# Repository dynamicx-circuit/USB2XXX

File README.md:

# USB2XXX
使用SL2.1S的一拖四USB方案，包含两个can接口，一个串口和一个DBUS接口

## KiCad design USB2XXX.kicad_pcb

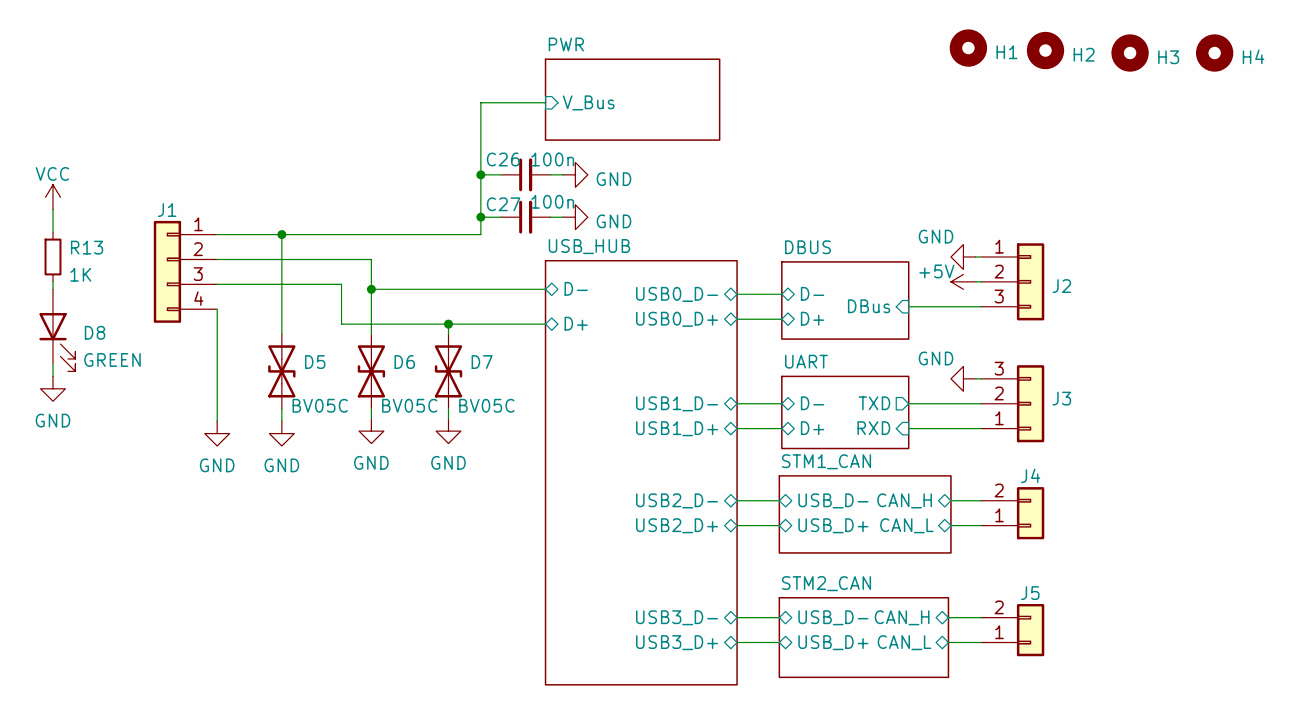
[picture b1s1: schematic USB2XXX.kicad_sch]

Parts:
C26, C27: 100n; C_0603_1608Metric
D5, D6, D7: BV05C; D_SOD-323
D8: GREEN; LED_0603_1608Metric
H1, H2, H3, H4: MountingHole; MountingHole_2.7mm_M2.5
J1: Conn_01x04; Molex_CLIK-Mate_502386-0470_1x04-1MP_P1.25mm_Horizontal
J2, J3: Conn_01x03; JST_GH_SM03B-GHS-TB_1x03-1MP_P1.25mm_Horizontal
J4, J5: Conn_01x02; JST_GH_SM02B-GHS-TB_1x02-1MP_P1.25mm_Horizontal
R13: 1K; R_0603_1608Metric

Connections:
+5V: C26.1, C27.1, D5.2 (A2), J1.1, J2.2; also elsewhere on the board
/DBUS/DBus: J2.3; also elsewhere on the board
/STM1_CAN/CAN_H: J4.2; also elsewhere on the board
/STM1_CAN/CAN_L: J4.1; also elsewhere on the board
/STM2_CAN/CAN_H: J5.2; also elsewhere on the board
/STM2_CAN/CAN_L: J5.1; also elsewhere on the board
/UART/RXD: J3.1; also elsewhere on the board
/UART/TXD: J3.2; also elsewhere on the board
/USB_HUB/D-: D6.2 (A2), J1.2; also elsewhere on the board
GND: C26.2, C27.2, D5.1 (A1), D6.1 (A1), D7.1 (A1), D8.1 (K), J1.4, J2.1, J3.3; also elsewhere on the board
unnamed: D8.2 (A), R13.2

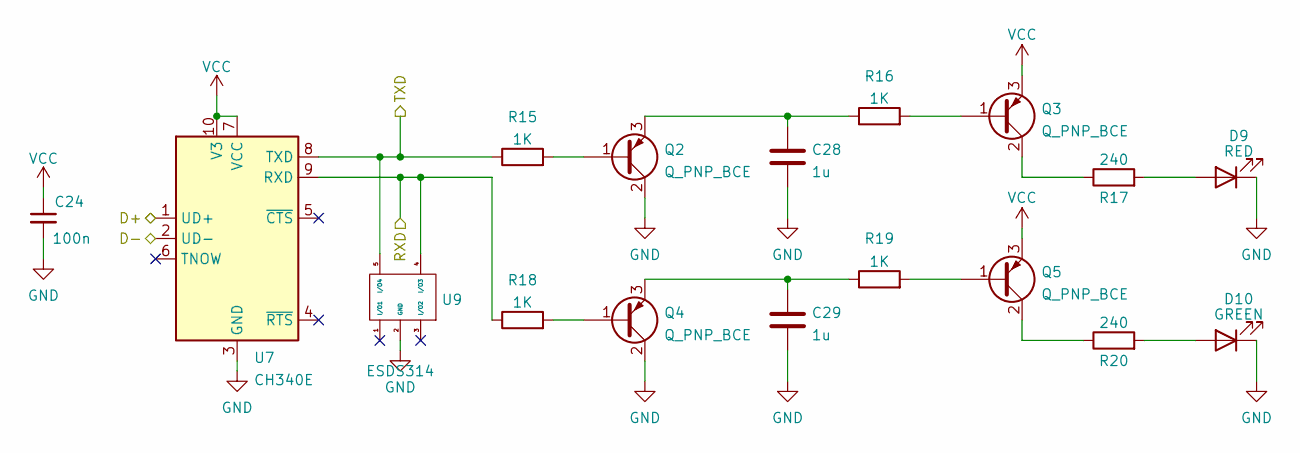
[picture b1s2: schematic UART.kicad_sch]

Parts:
C24: 100n; C_0603_1608Metric
C28, C29: 1u; C_0603_1608Metric
D9: RED; LED_0603_1608Metric
D10: GREEN; LED_0603_1608Metric
Q2, Q3, Q4, Q5: Q_PNP_BCE; SOT-23
R15, R16, R18, R19: 1K; R_0603_1608Metric
R17, R20: 240; R_0603_1608Metric
U7: CH340E; MSOP-10_3x3mm_P0.5mm
U9: ESDS314; SOT-23-5

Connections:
/UART/D+: U7.1 (UD+); also elsewhere on the board
/UART/D-: U7.2 (UD-); also elsewhere on the board
/UART/RXD: R18.1, U7.9 (RXD), U9.4 (I/O3); also elsewhere on the board
/UART/TXD: R15.1, U7.8 (TXD), U9.5 (I/O4); also elsewhere on the board
GND: C24.2, C28.2, C29.2, D9.1 (K), D10.1 (K), Q2.2 (C), Q4.2 (C), U7.3 (GND), U9.2 (GND); also elsewhere on the board
unnamed: D9.2 (A), R17.2
unnamed: D10.2 (A), R20.2
unnamed: Q2.1 (B), R15.2
unnamed: C28.1, Q2.3 (E), R16.1
unnamed: Q3.1 (B), R16.2
unnamed: Q3.2 (C), R17.1
unnamed: Q4.1 (B), R18.2
unnamed: C29.1, Q4.3 (E), R19.1
unnamed: Q5.1 (B), R19.2
unnamed: Q5.2 (C), R20.1

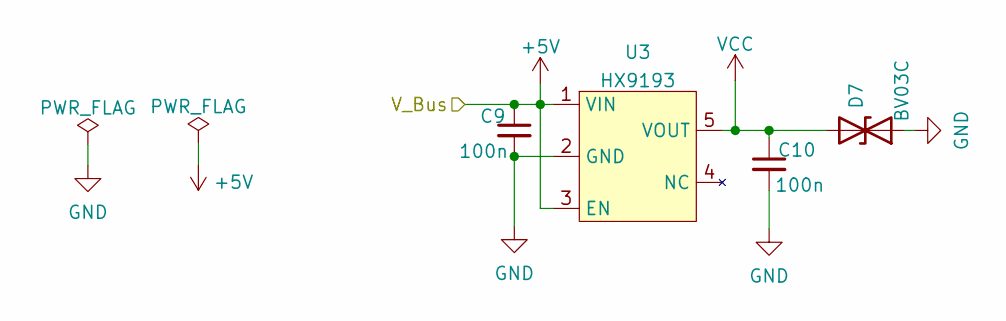
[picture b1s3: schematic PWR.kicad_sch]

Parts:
C9, C10: 100n; C_0603_1608Metric
D7: BV03C; D_SOD-323
U3: HX9193; SOT-23-5_HandSoldering

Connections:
+5V: C9.1, U3.1 (VIN), U3.3 (EN); also elsewhere on the board
GND: C9.2, C10.2, D7.1 (A1), U3.2 (GND); also elsewhere on the board

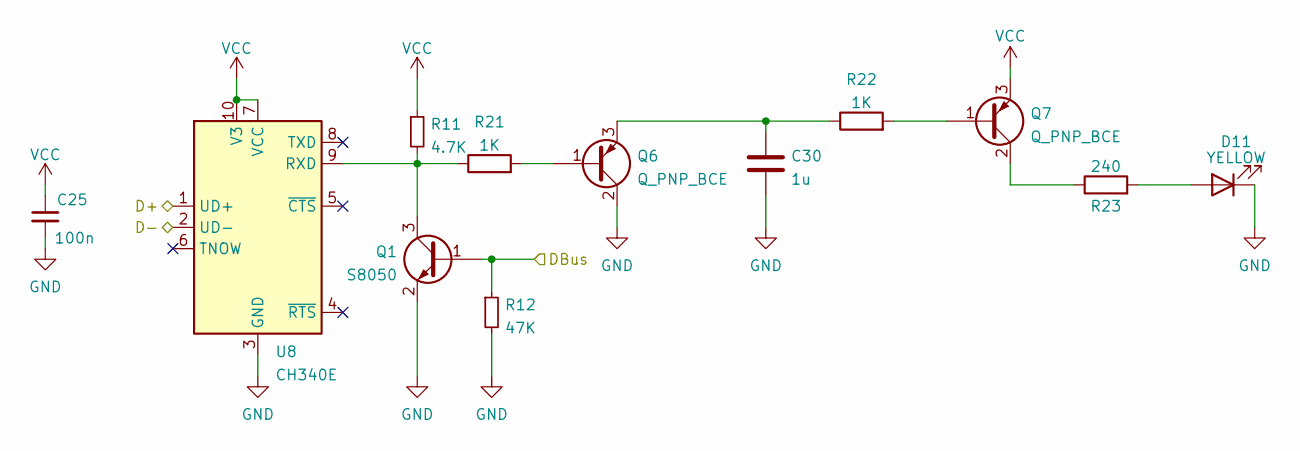
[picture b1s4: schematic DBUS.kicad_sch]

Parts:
C25: 100n; C_0603_1608Metric
C30: 1u; C_0603_1608Metric
D11: YELLOW; LED_0603_1608Metric
Q1: S8050; SOT-23
Q6, Q7: Q_PNP_BCE; SOT-23
R11: 4.7K; R_0603_1608Metric
R12: 47K; R_0603_1608Metric
R21, R22: 1K; R_0603_1608Metric
R23: 240; R_0603_1608Metric
U8: CH340E; MSOP-10_3x3mm_P0.5mm

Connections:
/DBUS/D+: U8.1 (UD+); also elsewhere on the board
/DBUS/D-: U8.2 (UD-); also elsewhere on the board
/DBUS/DBus: Q1.1 (B), R12.1; also elsewhere on the board
GND: C25.2, C30.2, D11.1 (K), Q1.2 (E), Q6.2 (C), R12.2, U8.3 (GND); also elsewhere on the board
unnamed: D11.2 (A), R23.2
unnamed: Q1.3 (C), R11.2, R21.1, U8.9 (RXD)
unnamed: Q6.1 (B), R21.2
unnamed: C30.1, Q6.3 (E), R22.1
unnamed: Q7.1 (B), R22.2
unnamed: Q7.2 (C), R23.1

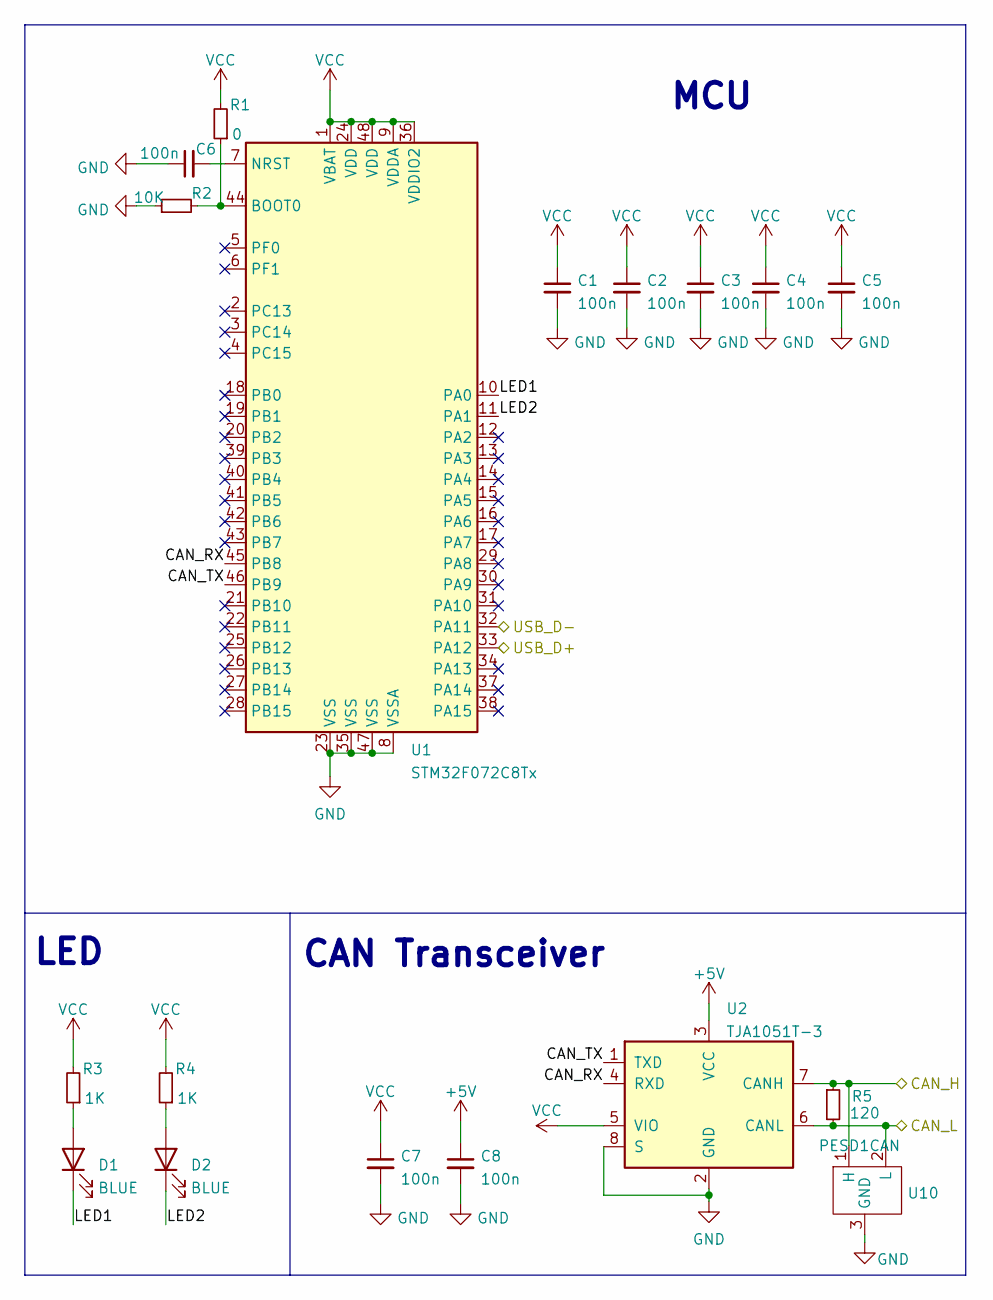
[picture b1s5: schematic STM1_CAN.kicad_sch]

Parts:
C1, C2, C3, C4, C5, C6, C7, C8: 100n; C_0603_1608Metric
D1, D2: BLUE; LED_0603_1608Metric
R1: 0; R_0603_1608Metric
R2: 10K; R_0603_1608Metric
R3, R4: 1K; R_0603_1608Metric
R5: 120; R_0603_1608Metric
U1: STM32F072C8Tx; LQFP-48_7x7mm_P0.5mm
U2: TJA1051T-3; SOIC-8_3.9x4.9mm_P1.27mm
U10: PESD1CAN; SOT-23-3

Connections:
+5V: C8.1, U2.3 (VCC); also elsewhere on the board
/STM1_CAN/CAN_H: R5.1, U2.7 (CANH), U10.1 (H); also elsewhere on the board
/STM1_CAN/CAN_L: R5.2, U2.6 (CANL), U10.2 (L); also elsewhere on the board
/STM1_CAN/CAN_RX: U1.45 (PB8), U2.4 (RXD)
/STM1_CAN/CAN_TX: U1.46 (PB9), U2.1 (TXD)
/STM1_CAN/LED1: D1.1 (K), U1.10 (PA0)
/STM1_CAN/LED2: D2.1 (K), U1.11 (PA1)
/STM1_CAN/USB_D+: U1.33 (PA12); also elsewhere on the board
/STM1_CAN/USB_D-: U1.32 (PA11); also elsewhere on the board
GND: C1.2, C2.2, C3.2, C4.2, C5.2, C6.1, C7.2, C8.2, R2.1, U1.8 (VSSA), U1.23 (VSS), U1.35 (VSS), U1.47 (VSS), U2.2 (GND), U2.8 (S), U10.3 (GND); also elsewhere on the board
unnamed: D1.2 (A), R3.1
unnamed: D2.2 (A), R4.1
unnamed: R1.1, R2.2, U1.44 (BOOT0)
unnamed: C6.2, U1.7 (NRST)

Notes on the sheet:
CAN Transceiver
LED
MCU

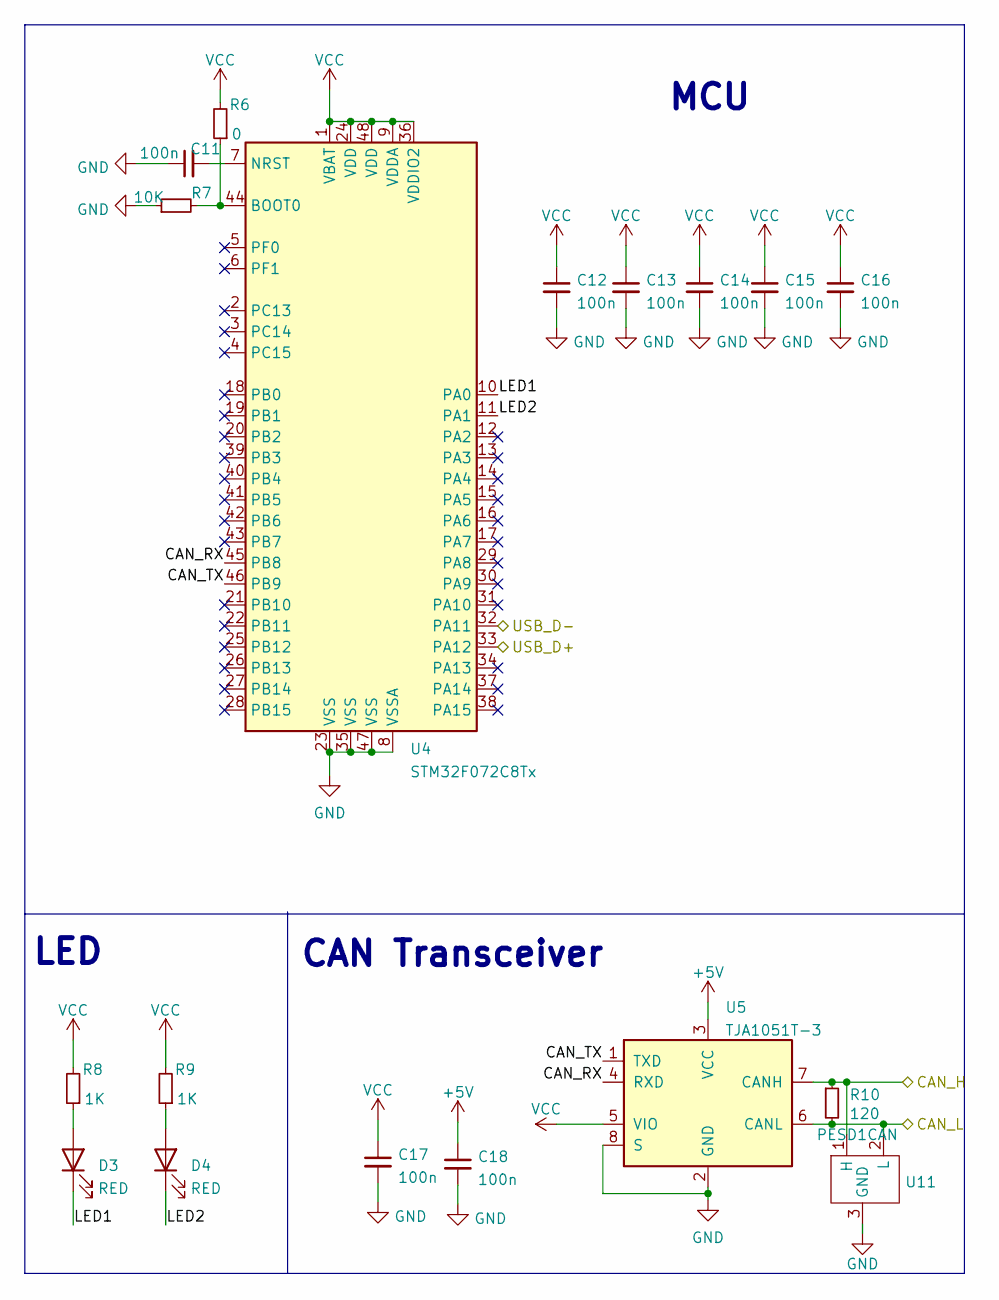
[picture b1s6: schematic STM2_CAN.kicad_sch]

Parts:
C11, C12, C13, C14, C15, C16, C17, C18: 100n; C_0603_1608Metric
D3, D4: RED; LED_0603_1608Metric
R6: 0; R_0603_1608Metric
R7: 10K; R_0603_1608Metric
R8, R9: 1K; R_0603_1608Metric
R10: 120; R_0603_1608Metric
U4: STM32F072C8Tx; LQFP-48_7x7mm_P0.5mm
U5: TJA1051T-3; SOIC-8_3.9x4.9mm_P1.27mm
U11: PESD1CAN; SOT-23-3

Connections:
+5V: C18.1, U5.3 (VCC); also elsewhere on the board
/STM2_CAN/CAN_H: R10.1, U5.7 (CANH), U11.1 (H); also elsewhere on the board
/STM2_CAN/CAN_L: R10.2, U5.6 (CANL), U11.2 (L); also elsewhere on the board
/STM2_CAN/CAN_RX: U4.45 (PB8), U5.4 (RXD)
/STM2_CAN/CAN_TX: U4.46 (PB9), U5.1 (TXD)
/STM2_CAN/LED1: D3.1 (K), U4.10 (PA0)
/STM2_CAN/LED2: D4.1 (K), U4.11 (PA1)
/STM2_CAN/USB_D+: U4.33 (PA12); also elsewhere on the board
/STM2_CAN/USB_D-: U4.32 (PA11); also elsewhere on the board
GND: C11.1, C12.2, C13.2, C14.2, C15.2, C16.2, C17.2, C18.2, R7.1, U4.8 (VSSA), U4.23 (VSS), U4.35 (VSS), U4.47 (VSS), U5.2 (GND), U5.8 (S), U11.3 (GND); also elsewhere on the board
unnamed: D3.2 (A), R8.1
unnamed: D4.2 (A), R9.1
unnamed: R6.1, R7.2, U4.44 (BOOT0)
unnamed: C11.2, U4.7 (NRST)

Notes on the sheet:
LED
MCU
CAN Transceiver

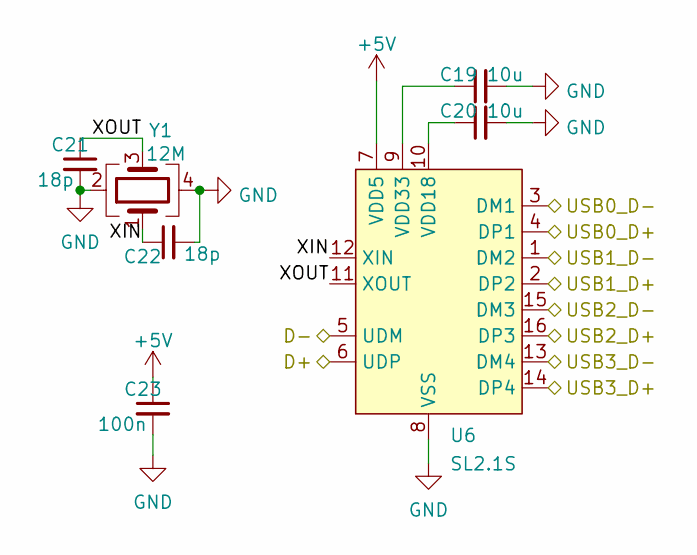
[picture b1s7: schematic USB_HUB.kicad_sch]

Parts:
C19, C20: 10u; C_0603_1608Metric
C21, C22: 18p; C_0603_1608Metric
C23: 100n; C_0603_1608Metric
U6: SL2.1S; SL2.1S-SSOP-16
Y1: 12M; Crystal_SMD_3225-4Pin_3.2x2.5mm

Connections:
+5V: C23.1, U6.7 (VDD5); also elsewhere on the board
/DBUS/D+: U6.4 (DP1); also elsewhere on the board
/DBUS/D-: U6.3 (DM1); also elsewhere on the board
/STM1_CAN/USB_D+: U6.16 (DP3); also elsewhere on the board
/STM1_CAN/USB_D-: U6.15 (DM3); also elsewhere on the board
/STM2_CAN/USB_D+: U6.14 (DP4); also elsewhere on the board
/STM2_CAN/USB_D-: U6.13 (DM4); also elsewhere on the board
/UART/D+: U6.2 (DP2); also elsewhere on the board
/UART/D-: U6.1 (DM2); also elsewhere on the board
/USB_HUB/D-: U6.5 (UDM); also elsewhere on the board
/USB_HUB/XIN: C22.1, U6.12 (XIN), Y1.1
/USB_HUB/XOUT: C21.1, U6.11 (XOUT), Y1.3
GND: C19.2, C20.2, C21.2, C22.2, C23.2, U6.8 (VSS), Y1.2, Y1.4; also elsewhere on the board
unnamed: C20.1, U6.10 (VDD18)
unnamed: C19.1, U6.9 (VDD33)

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
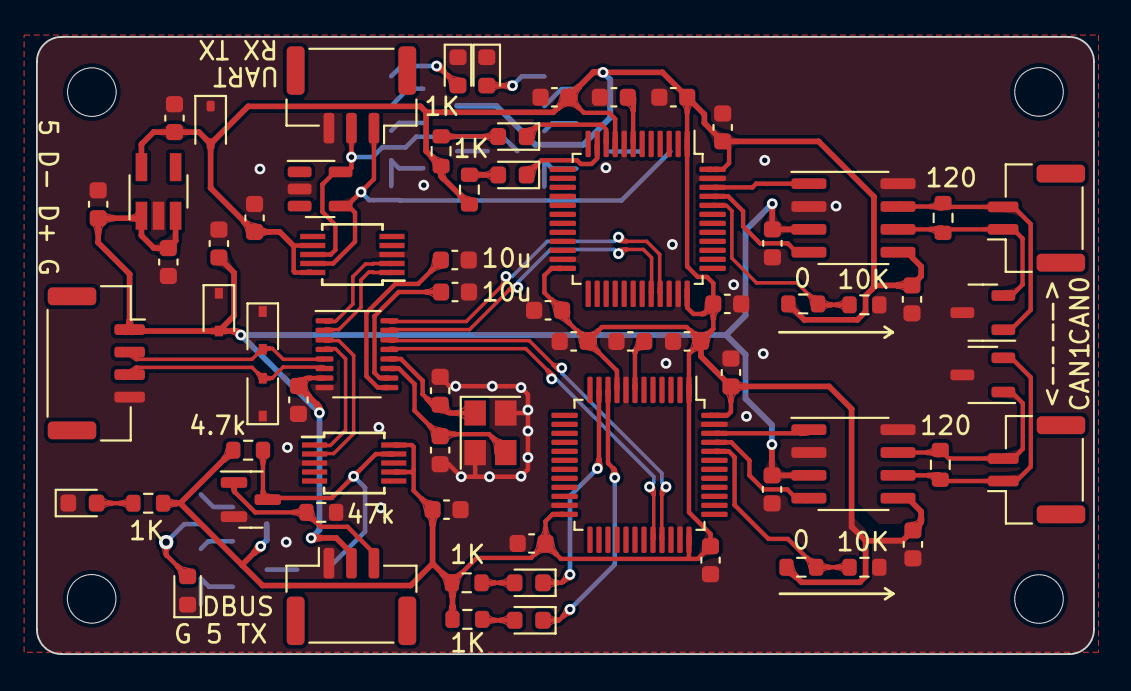
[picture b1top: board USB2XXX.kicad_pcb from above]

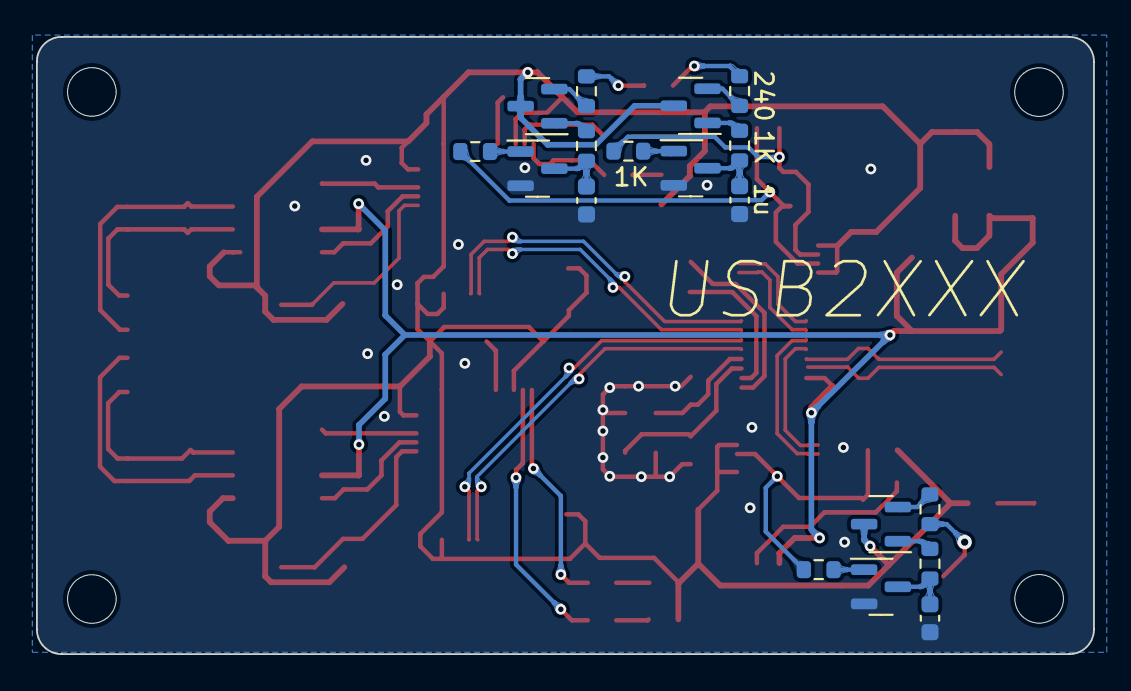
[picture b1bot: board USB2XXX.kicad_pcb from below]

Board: 2 copper layers, 58.7 x 34.3 mm, 92 parts (18 on the bottom side), 57 nets.

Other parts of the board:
D12: BV03C; D_SOD-323

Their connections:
GND: D12.1 (A1); also elsewhere on the board

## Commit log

2022-07-01 Add .gitignore and README.md
2022-07-01 Add USB2XXX original version
2022-07-01 Update and delete
    Updata .gitignore
    Delete USB2XXX.kicad_prl
2023-04-15 Big update on UART-pilot lamp/routings/connectors/esd protection
2023-04-25 Change connectors back to GH1.25&Add ESD for UART and CAN
2023-06-23 Adaption for SMT
2023-06-23 Adaption for SMT(hotfix)
